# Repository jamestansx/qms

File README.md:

# Queue Management System

## TODO
- [x] update queue to wearables to vibrate
- [x] fix bug where queue is not updating its priority

## SETUP

- User UI:
```sh
$ # To run the app
$ fvm flutter run --dart-define=BASEURL=<api-url>
$ # To build the app
$ fvm flutter build apk --release --dart-define=BASEURL=<api-url>
```

- Management UI:
```sh
$ # To run the app (optionally --release)
$ fvm flutter run -d web-server --web-port 8080 --web-hostname 0.0.0.0 --dart-define=BASEURL=<api-url>
```

- backend:
```sh
$ # To start the server
$ BASEURL=<api-url> cargo run --release
```

- firmware:
```sh
$ # Only for arduino-cli
$ ./build.sh <port-name>
```

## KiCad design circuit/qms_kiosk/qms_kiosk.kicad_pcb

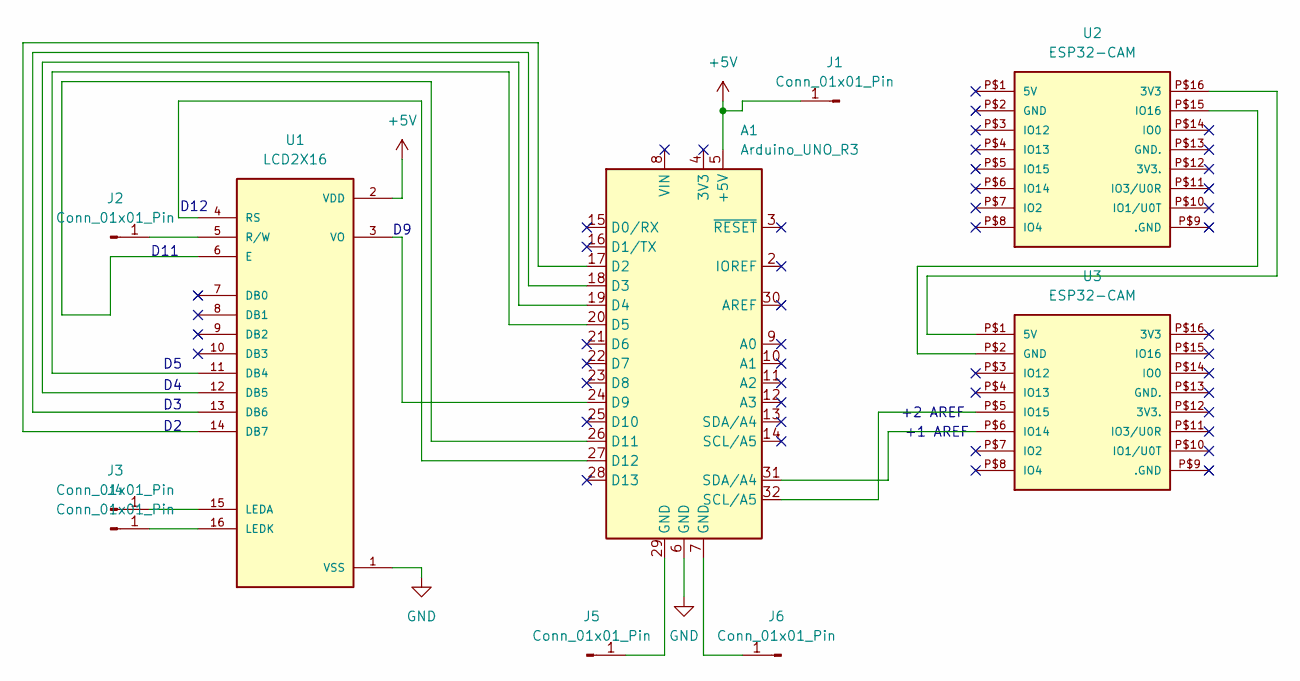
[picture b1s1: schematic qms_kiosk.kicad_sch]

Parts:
A1: Arduino_UNO_R3
J1, J2, J3, J4, J5, J6: Conn_01x01_Pin; PinHeader_1x01_P2.00mm_Vertical
U1: LCD2X16; LCD_LCD2X16; PARTREV 0
U2, U3: ESP32-CAM

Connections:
+5V: A1.5 (+5V), J1.1, U1.2 (VDD)
GND: A1.6 (GND), U1.1 (VSS)
unnamed: A1.17 (D2), U1.14 (DB7)
unnamed: A1.18 (D3), U1.13 (DB6)
unnamed: A1.19 (D4), U1.12 (DB5)
unnamed: A1.20 (D5), U1.11 (DB4)
unnamed: A1.24 (D9), U1.3 (VO)
unnamed: A1.26 (D11), U1.6 (E)
unnamed: A1.27 (D12), U1.4 (RS)
unnamed: J2.1, U1.5 (R/W)
unnamed: J3.1, U1.15 (LEDA)
unnamed: J4.1, U1.16 (LEDK)
unnamed: A1.29 (GND), J5.1
unnamed: A1.7 (GND), J6.1
unnamed: U2.P$16 (3V3), U3.P$1 (5V)
unnamed: U2.P$15 (IO16), U3.P$2 (GND)
unnamed: A1.31 (SDA/A4), U3.P$6 (IO14)
unnamed: A1.32 (SCL/A5), U3.P$5 (IO15)

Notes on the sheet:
D11
+2 AREF
+1 AREF
D12

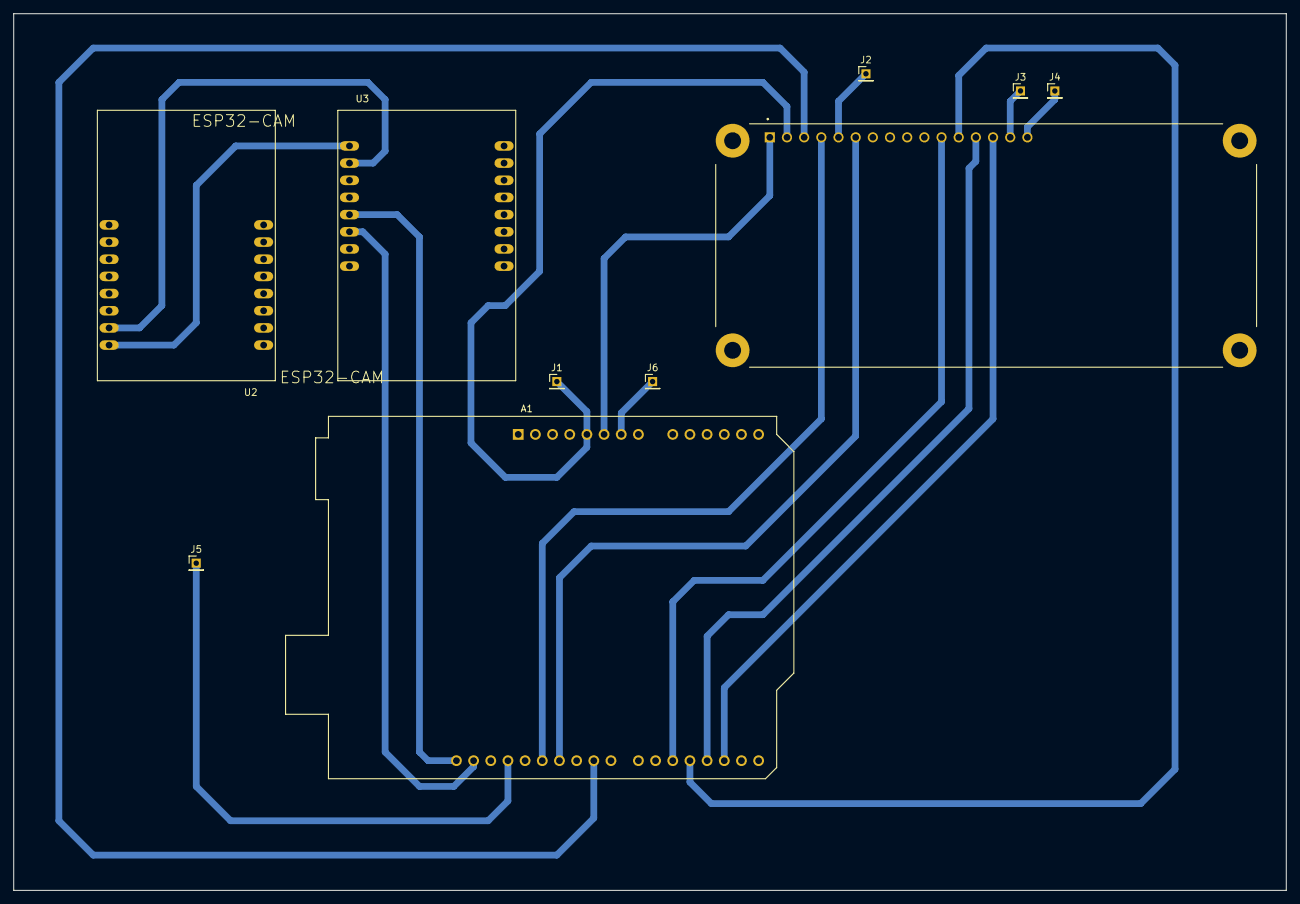
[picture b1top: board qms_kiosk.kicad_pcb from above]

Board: 2 copper layers, 188.2 x 129.7 mm, 10 parts (0 on the bottom side), 18 nets.

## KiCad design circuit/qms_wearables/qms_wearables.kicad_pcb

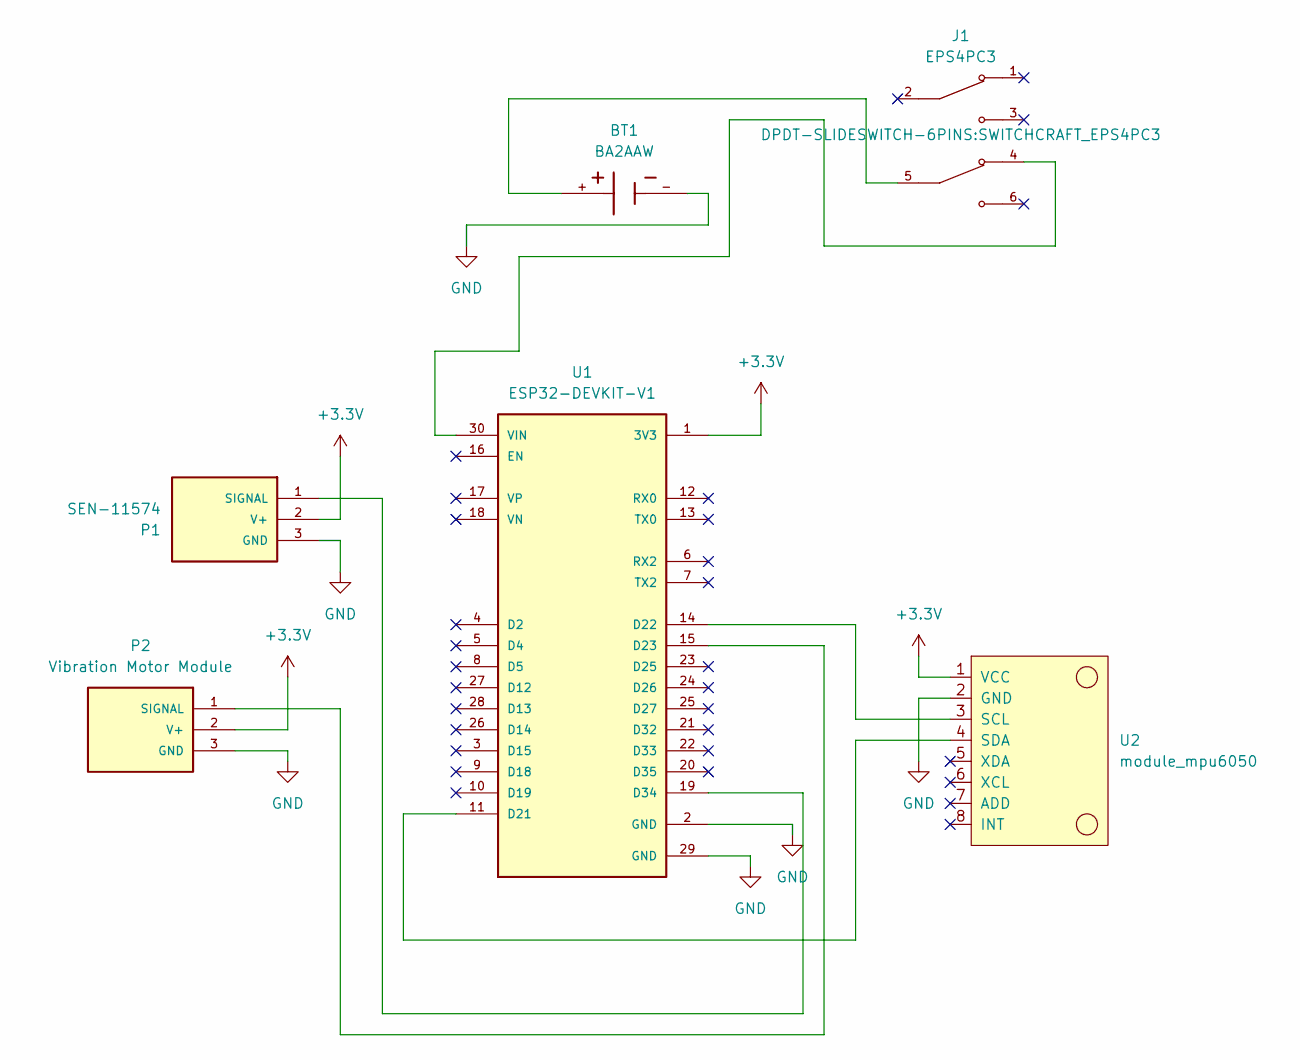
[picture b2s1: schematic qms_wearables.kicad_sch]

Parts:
BT1: BA2AAW; BAT_BA2AAW; PARTREV E
J1: EPS4PC3; SWITCHCRAFT_EPS4PC3
P1: SEN-11574; XDCR_SEN-11574
P2: Vibration Motor Module; XDCR_Vibration_Motor_Module
U1: ESP32-DEVKIT-V1; MODULE_ESP32_DEVKIT_V1; PARTREV N/A
U2: module_mpu6050

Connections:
+3.3V: P1.2 (V+), P2.2 (V+), U1.1 (3V3), U2.1 (VCC)
GND: BT1.-, P1.3 (GND), P2.3 (GND), U1.2 (GND), U1.29 (GND), U2.2 (GND)
unnamed: BT1.+, J1.5
unnamed: P1.1 (SIGNAL), U1.19 (D34)
unnamed: P2.1 (SIGNAL), U1.15 (D23)
unnamed: U1.11 (D21), U2.4 (SDA)
unnamed: U1.14 (D22), U2.3 (SCL)
unnamed: J1.4, U1.30 (VIN)

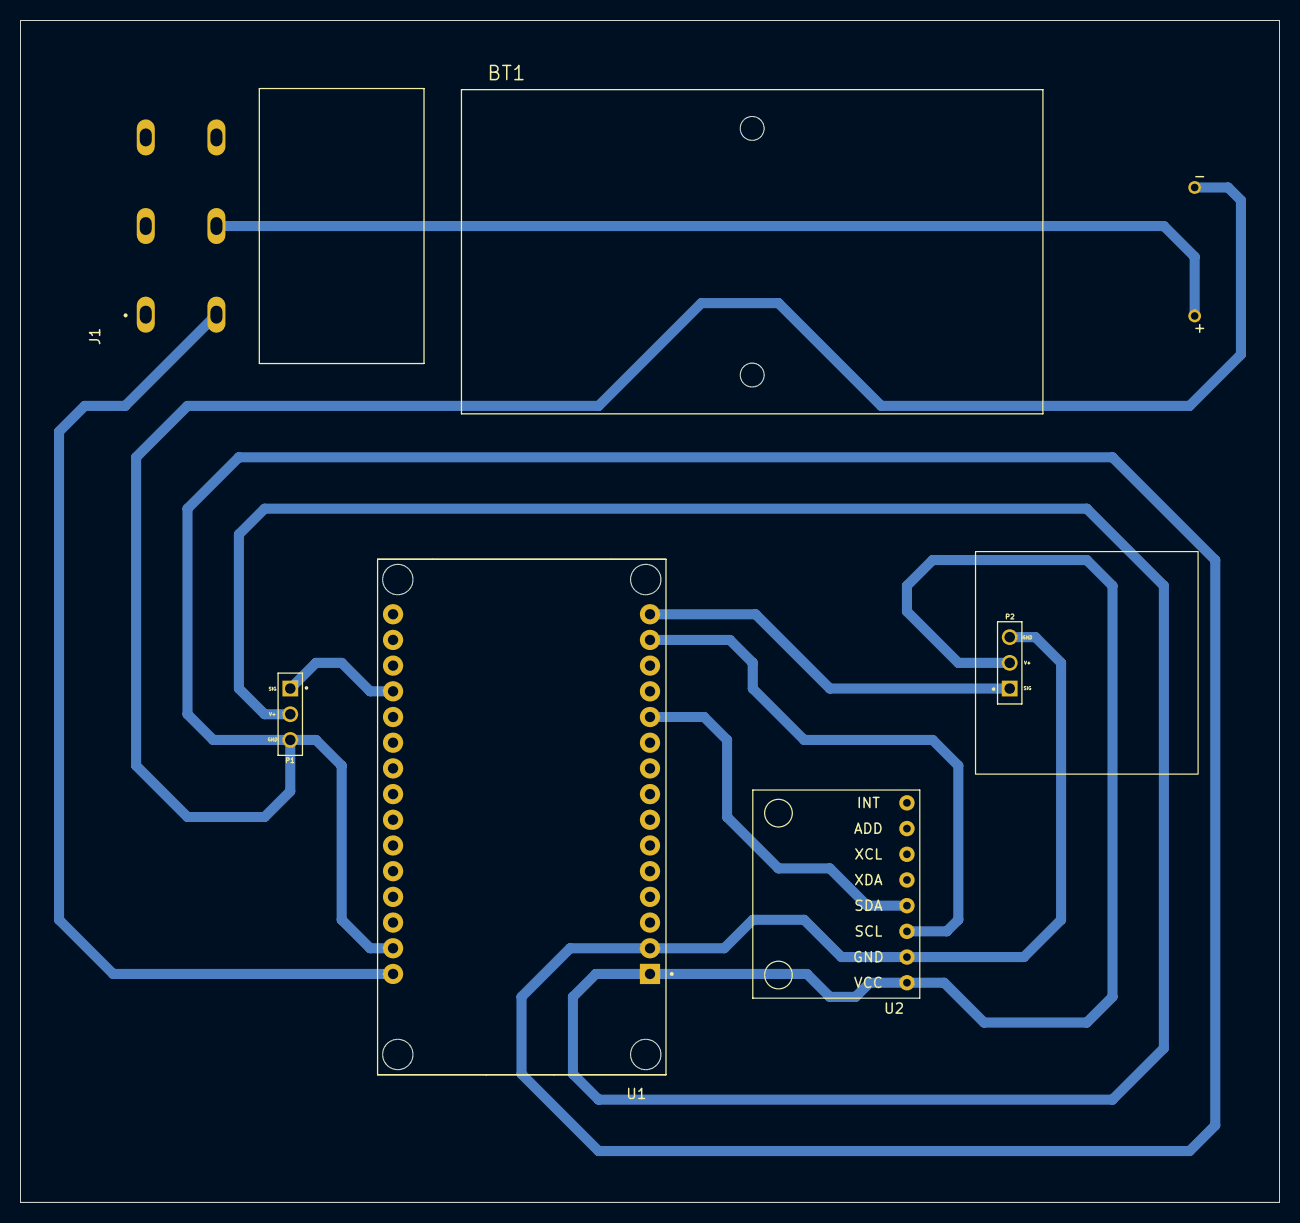
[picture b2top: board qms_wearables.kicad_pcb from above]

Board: 2 copper layers, 124.5 x 116.8 mm, 6 parts (0 on the bottom side), 8 nets.

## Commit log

2024-11-15 Ready. Set. Go!
2024-11-15 Update Readme files
2024-11-16 chore: ignore fp-info-cache
    ref: https://www.mail-archive.com/kicad-developers@lists.launchpad.net/msg32871.html
2024-11-16 feat: Add SEN_11574 symbol and footprint
2024-11-16 Add ESP32-DEVKIT-V1 symbol and footprint
2024-11-16 feat: Add MPU6050 breakout board
2024-11-16 feat: Add LCD 16x4(16x2) Display symbol and footprint
2024-11-17 feat: Add ESP32-CAM symbol and footprint
2024-11-17 feat: Add I2C module for LCD Display symbol and footprint.
2024-11-17 Draft 1: Design schematic circuit of Kiosk Machine.
2024-11-17 Draft 1 (Wearables): Design schematic circuit of Wearables.
2024-11-17 chore: for god sake ignore irrelevant files
2024-11-17 chore: clear git cache
    to ignore gitignore-ed files
2024-11-17 fix: wrong input voltage to ESP32
2024-11-23 wip: testing websocket for backend server
2024-11-23 wip: init firmware
2024-11-23 feat: hello axum
2024-11-23 wip: add patient registration endpoint
2024-11-24 Draft 1 (Kiosk): Set up Send and Receive communication betweenESP32-CAM and Arduino UNO.
2024-12-02 refactor: restructure backend files
2024-12-02 fix: constraint appointment PK key non NULL
2024-12-02 fix: add autoincrement and not null to id field
2024-12-04 wip: initial queue service
2024-12-05 wip: queue status is able to broadcast
2024-12-06 wip: Determine the signal strength between server and client esp32 ble.
2024-12-06 wip: Testing the basic integration between LCD and WEMOS D1 R1 ESP8266.
2024-12-07 wip: Testing the MQTT for Heart Sensor and Accelerometer.
2024-12-12 minimal example of mqtt client
2024-12-21 wip: Modified the formula of Acceleration magnitude and angular velocity to prevent the fall detection when the accelerometer is twisted in stationary.
2024-12-21 wip: Modified the delay at L93 for preventing blocking function.
2024-12-21 wip: Modified the Kiosk system schematic circuit.
2024-12-23 wip: Update the pcb footprint of the components.
2024-12-23 wip: Modified the formula of acceleration magnitude and angular velocity magnitude
2024-12-23 wip: Update the pcb footprint of the components in wearables circuit.
2024-12-26 wip: First draft complete kiosk circuit.
2024-12-26 wip: First draft complete wearable circuit schematic and pcb with adding 2x battery, DC vibration motor module.
2024-12-28 wip: Second draft with replacing the schematic and footprint of vibration motor module
2024-12-28 wip: Replacing the code of accelerometer with changing formulae of acceleration magnitude.
2024-12-29 remove mqtt test project
2024-12-29 add password login
2024-12-29 rewrite backend...
2024-12-29 wip: initial ui completed, left queue status
2024-12-29 fix various backend issues
2024-12-29 init frontend project
2024-12-30 feat: filter appointment list and display queue no. only on status
2024-12-30 wip: Second draft with reducing size of the edge cuts to fulfill the pcb board physical dimension 15cm by 30cm
2024-12-30 wip: Third draft with reducing size of the edge cuts as smaller as possible
2024-12-30 wip: Third draft with reducing size of the edge cuts in wearables pcb as smaller as possible
2024-12-31 wip: Fourth draft with replacing the DPDT Slide Switch and 2 Cell battery footprint and schematic circuit.
2024-12-31 wip: Draft for changing the pcb traces size from 0.762mm (T30) to 0.508mm(T20).
2024-12-31 Ready. Set. Go Hospital UI!
2024-12-31 add cors middleware to axum
2024-12-31 integrate iot to server
    expected incoming bugs -.-
2024-12-31 FUCK
2024-12-31 wip: staff ui...
2025-01-04 feat: send topic to monitor
2025-01-04 feat: hospital ui
2025-01-04 wip: First draft complete coding for wearables (Testing using MQTT Broker.
2025-01-04 wip: First draft complete coding for ESP32-CAM and LCD Displayof kiosk machine (Testing using MQTT Broker).
2025-01-04 wip: Fifth draft change the trace size into 1mm for pcb fabrication requirement, (mistake: the distance between drill holes in the overall circuit are too short, which cause the real components canno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
2025-01-04 feat: add api callback for buttons
2025-01-04 feat: add queue alert notification
2025-01-05 update port to 8000
2025-01-05 update port
2025-01-05 fix: SSE not able to connect
2025-01-05 feat: replace real_time_chart with graphics
2025-01-06 Remove the vibration feature on Heart Rate measurement and move to the mqtt subscribe part
2025-01-06 feat: send message to verifier
2025-01-06 feat: I don't know if it works
2025-01-06 fixup! feat: I don't know if it works
2025-01-06 fixup! fixup! feat: I don't know if it works
2025-01-06 feat: add appointment on staff ui
2025-01-07 fix: update service uuids
2025-01-08 wip: modified the codes of server and wearables QMS
2025-01-08 wip: modified the codes of esp32-cam.
2025-01-09 feat: alert wearable on queue
2025-01-09 fix: tested bugs
2025-01-09 chore: rename files properly
2025-01-09 feat: add support to vibrate motor on queue
2025-01-10 BIG update
2025-01-10 fix: race condition on navigation and storing data when logging in
2025-01-11 feat: better UI (not really :-))
2025-01-12 feat: improve ui
2025-01-12 I guess it's all done?
2025-01-12 build: add build script
2025-01-13 feat: display assigned wearable in queue
    fix: current queue will not be overwritten
2025-01-13 format code
2025-01-13 letsssssssssss goooooooooo
2025-01-14 fix: do not add wearable field if no wearable
2025-01-14 chore: update device uuid
2025-01-14 fix: wtf bugs
2025-01-15 feat: add button to register new wearable
2025-01-17 test: add test case for priority queue
